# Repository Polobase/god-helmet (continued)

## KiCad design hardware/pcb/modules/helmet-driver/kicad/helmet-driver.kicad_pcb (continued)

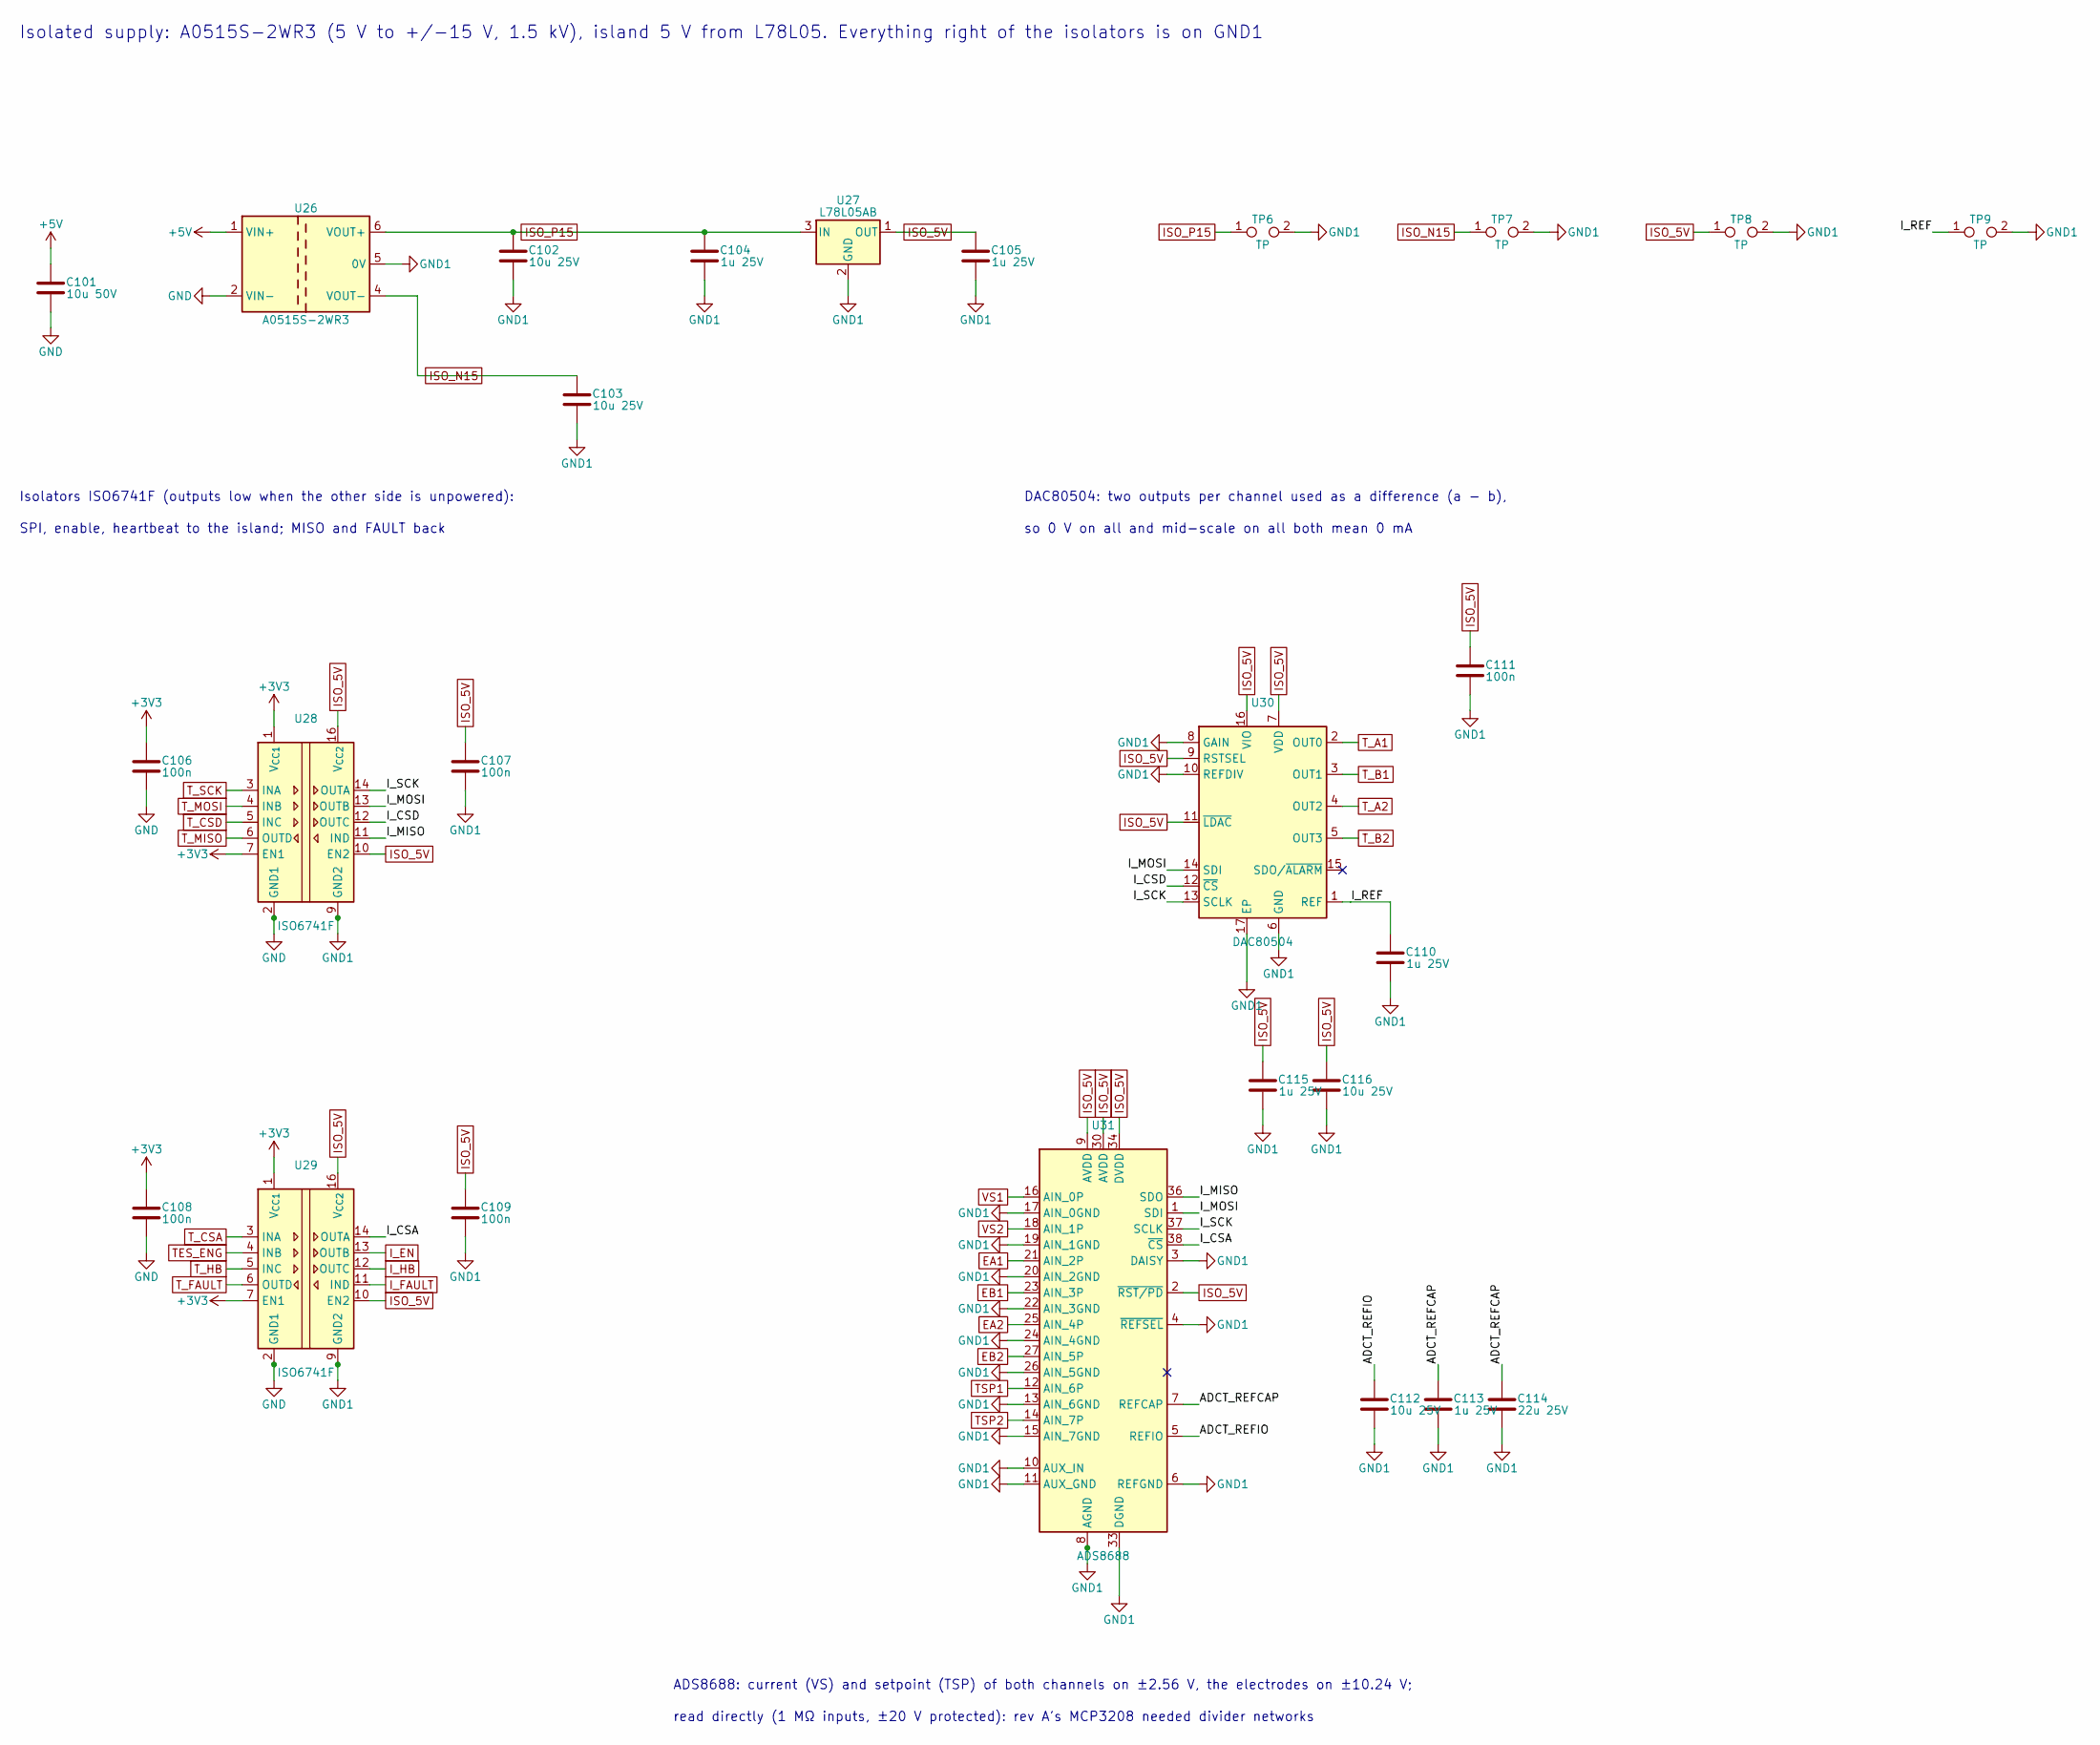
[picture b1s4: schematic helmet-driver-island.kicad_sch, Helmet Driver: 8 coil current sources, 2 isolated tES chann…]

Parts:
C101: 10u 50V; C_1206_3216Metric; MPN CL31A106KBHNNNE; LCSC C13585
C102, C103, C112, C116: 10u 25V; C_1210_3225Metric; MPN CL32B106KAJNNNE; LCSC C39232
C104, C105, C110, C113, C115: 1u 25V; C_0603_1608Metric; MPN CL10B105KA8NNNC; LCSC C29936
C106, C107, C108, C109, C111: 100n; C_0603_1608Metric; MPN CC0603KRX7R9BB104; LCSC C14663
C114: 22u 25V; C_1210_3225Metric; MPN CL32B226KAJNNNE; LCSC C309062
TP6, TP7, TP8, TP9: TP; TestPoint_2Pads_Pitch2.54mm_Drill0.8mm; PartKey testpoint-2pad
U26: A0515S-2WR3; Converter_DCDC_EVISUN_A0515S-2WR3_THT; MPN A0515S-2WR3; LCSC C7465204
U27: L78L05AB; SOT-89-3; MPN L78L05ABUTR; LCSC C42738
U28, U29: ISO6741F; SOIC-16W_7.5x10.3mm_P1.27mm; MPN ISO6741FDWR; LCSC C5216433
U30: DAC80504; Texas_RTE0016D_WQFN-16-1EP_3x3mm_P0.5mm_EP0.8x0.8mm_Thermal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; MPN DAC80504RTET; LCSC C2862796
U31: ADS8688; TSSOP-38_4.4x9.7mm_P0.5mm; MPN ADS8688IDBTR; LCSC C527390

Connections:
+3V3: C106.1, C108.1, U28.1 (V_{CC1}), U28.7 (EN1), U29.1 (V_{CC1}), U29.7 (EN1); also elsewhere on the board
+5V: C101.1, U26.1 (VIN+); also elsewhere on the board
/tES island: isolated power, isolators, DAC, ADC/ADCT_REFCAP: C113.1, C114.1, U31.7 (REFCAP)
/tES island: isolated power, isolators, DAC, ADC/ADCT_REFIO: C112.1, U31.5 (REFIO)
/tES island: isolated power, isolators, DAC, ADC/I_CSA: U29.14 (OUTA), U31.38 (~CS)
/tES island: isolated power, isolators, DAC, ADC/I_CSD: U28.12 (OUTC), U30.12 (~CS)
/tES island: isolated power, isolators, DAC, ADC/I_MISO: U28.11 (IND), U31.36 (SDO)
/tES island: isolated power, isolators, DAC, ADC/I_MOSI: U28.13 (OUTB), U30.14 (SDI), U31.1 (SDI)
/tES island: isolated power, isolators, DAC, ADC/I_REF: C110.1, TP9.1, U30.1 (REF)
/tES island: isolated power, isolators, DAC, ADC/I_SCK: U28.14 (OUTA), U30.13 (SCLK), U31.37 (SCLK)
EA1: U31.21 (AIN_2P); also elsewhere on the board
EA2: U31.25 (AIN_4P); also elsewhere on the board
EB1: U31.23 (AIN_3P); also elsewhere on the board
EB2: U31.27 (AIN_5P); also elsewhere on the board
GND: C101.2, C106.2, C108.2, U26.2 (VIN-), U28.2 (GND1), U28.8 (GND1), U29.2 (GND1), U29.8 (GND1); also elsewhere on the board
GND1: C102.2, C103.2, C104.2, C105.2, C107.2, C109.2, C110.2, C111.2, C112.2, C113.2, C114.2, C115.2, C116.2, TP6.2, TP7.2, TP8.2, TP9.2, U26.5 (0V), U27.2 (GND), U28.9 (GND2), U28.15 (GND2), U29.9 (GND2), U29.15 (GND2), U30.6 (GND), U30.8 (GAIN), U30.10 (REFDIV), U30.17 (EP), U31.3 (DAISY), U31.4 (~REFSEL), U31.6 (REFGND), U31.8 (AGND), U31.10 (AUX_IN), U31.11 (AUX_GND), U31.13 (AIN_6GND), U31.15 (AIN_7GND), U31.17 (AIN_0GND), U31.19 (AIN_1GND), U31.20 (AIN_2GND), U31.22 (AIN_3GND), U31.24 (AIN_4GND), U31.26 (AIN_5GND), U31.28 (AGND), U31.29 (AGND), U31.31 (AGND), U31.32 (AGND), U31.33 (DGND); also elsewhere on the board
ISO_5V: C105.1, C107.1, C109.1, C111.1, C115.1, C116.1, TP8.1, U27.1 (OUT), U28.10 (EN2), U28.16 (V_{CC2}), U29.10 (EN2), U29.16 (V_{CC2}), U30.7 (VDD), U30.9 (RSTSEL), U30.11 (~LDAC), U30.16 (VIO), U31.2 (~RST/PD), U31.9 (AVDD), U31.30 (AVDD), U31.34 (DVDD); also elsewhere on the board
ISO_N15: C103.1, TP7.1, U26.4 (VOUT-); also elsewhere on the board
ISO_P15: C102.1, C104.1, TP6.1, U26.6 (VOUT+), U27.3 (IN); also elsewhere on the board
I_EN: U29.13 (OUTB); also elsewhere on the board
I_FAULT: U29.11 (IND); also elsewhere on the board
I_HB: U29.12 (OUTC); also elsewhere on the board
TES_ENG: U29.4 (INB); also elsewhere on the board
TSP1: U31.12 (AIN_6P); also elsewhere on the board
TSP2: U31.14 (AIN_7P); also elsewhere on the board
T_A1: U30.2 (OUT0); also elsewhere on the board
T_A2: U30.4 (OUT2); also elsewhere on the board
T_B1: U30.3 (OUT1); also elsewhere on the board
T_B2: U30.5 (OUT3); also elsewhere on the board
T_CSA: U29.3 (INA); also elsewhere on the board
T_CSD: U28.5 (INC); also elsewhere on the board
T_FAULT: U29.6 (OUTD); also elsewhere on the board
T_HB: U29.5 (INC); also elsewhere on the board
T_MISO: U28.6 (OUTD); also elsewhere on the board
T_MOSI: U28.4 (INB); also elsewhere on the board
T_SCK: U28.3 (INA); also elsewhere on the board
VS1: U31.16 (AIN_0P); also elsewhere on the board
VS2: U31.18 (AIN_1P); also elsewhere on the board

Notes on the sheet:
read directly (1 MΩ inputs, ±20 V protected): rev A's MCP3208 needed divider networks
SPI, enable, heartbeat to the island; MISO and FAULT back
so 0 V on all and mid-scale on all both mean 0 mA
Isolated supply: A0515S-2WR3 (5 V to +/-15 V, 1.5 kV), island 5 V from L78L05. Everything right of the isolators is on GND1
Isolators ISO6741F (outputs low when the other side is unpowered):
DAC80504: two outputs per channel used as a difference (a - b),
ADS8688: current (VS) and setpoint (TSP) of both channels on ±2.56 V, the electrodes on ±10.24 V;

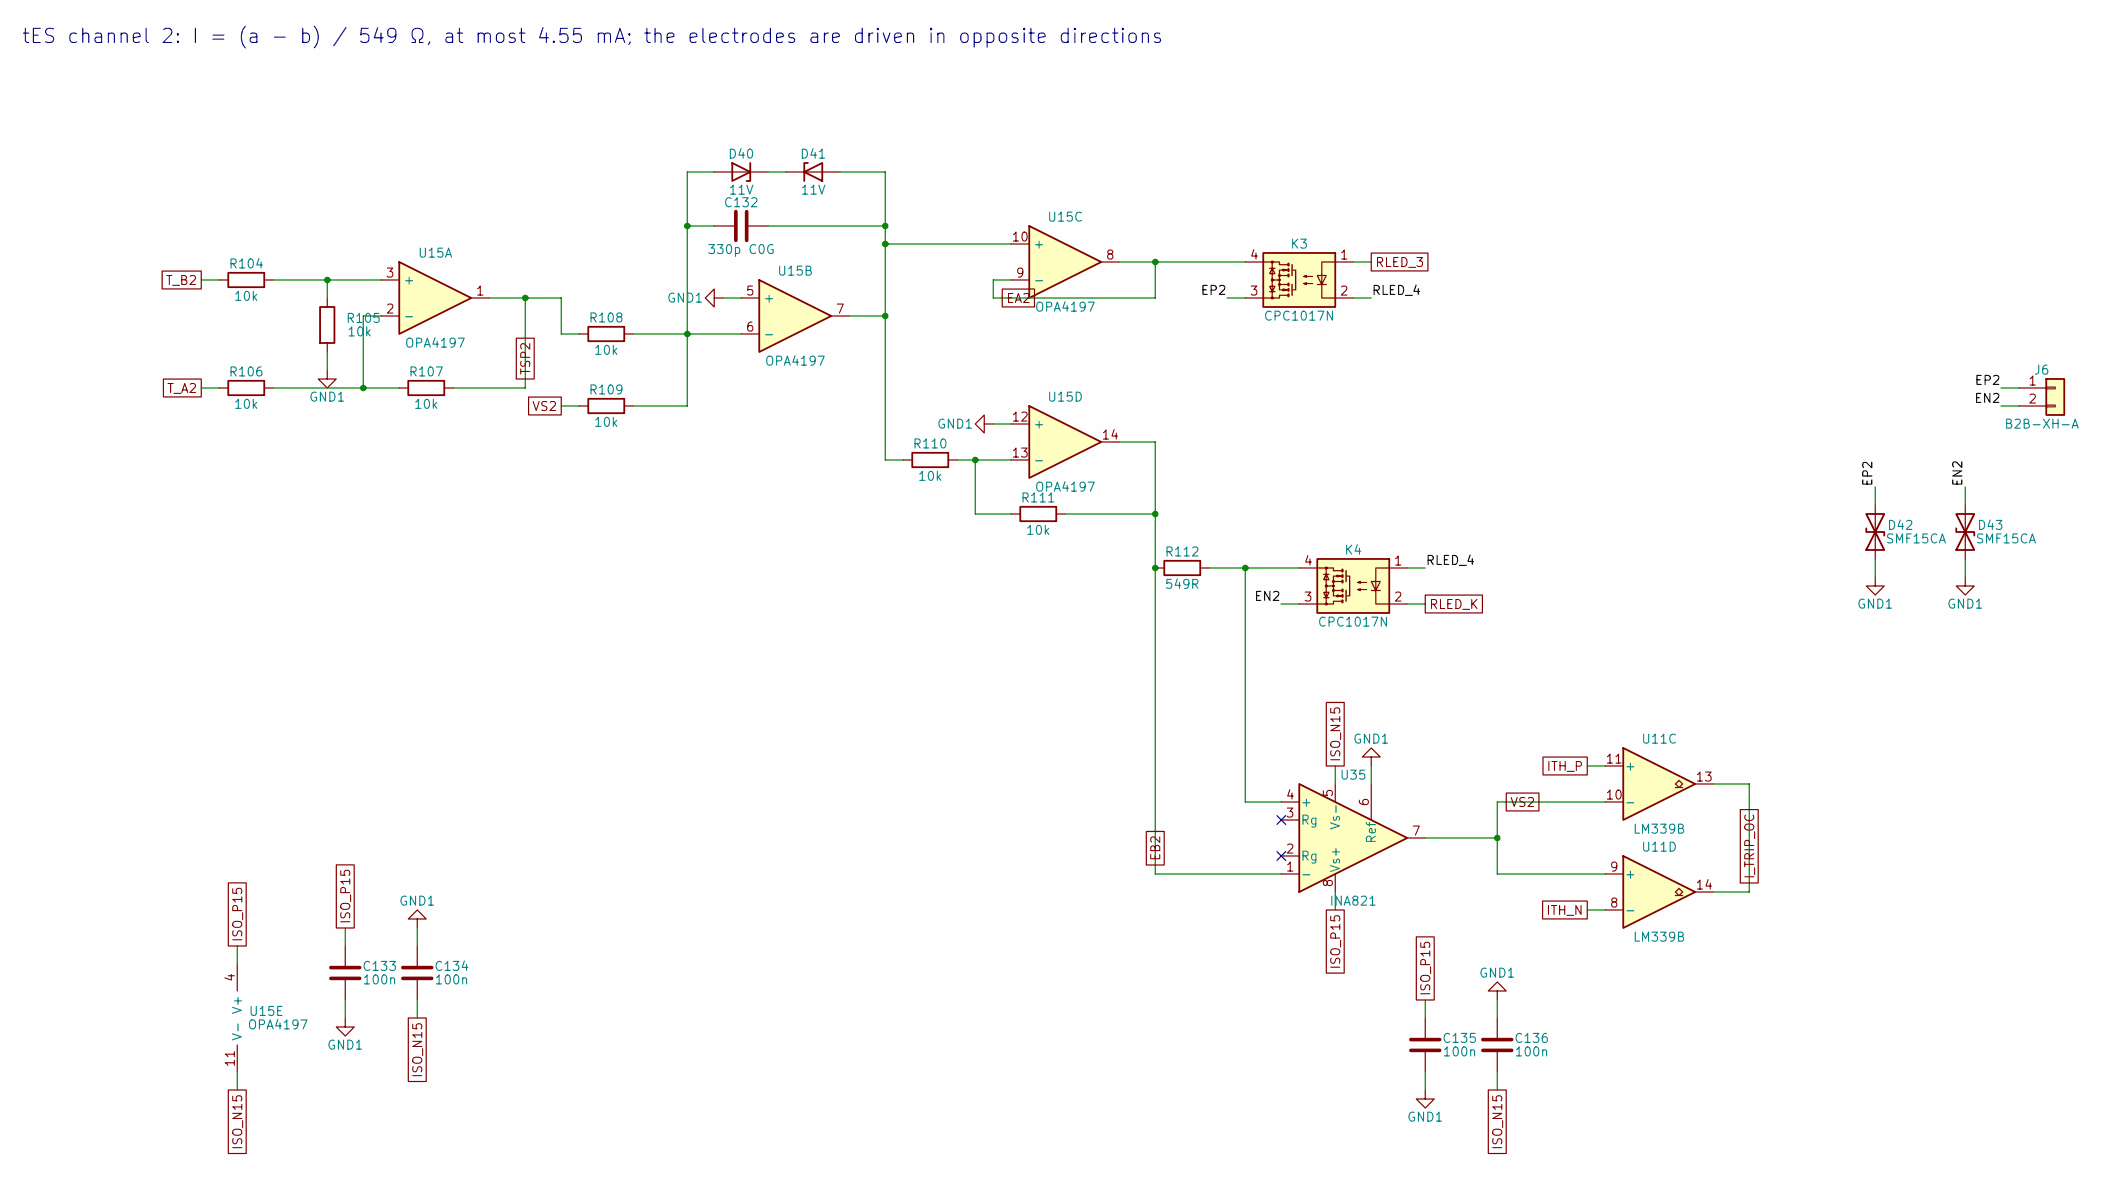
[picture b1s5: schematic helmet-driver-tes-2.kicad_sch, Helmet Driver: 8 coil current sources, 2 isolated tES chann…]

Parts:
C132: 330p C0G; C_0603_1608Metric; MPN 0603CG331J500NT; LCSC C190577
C133, C134, C135, C136: 100n; C_0603_1608Metric; MPN CC0603KRX7R9BB104; LCSC C14663
D40, D41: 11V; D_SOD-123; MPN BZT52C11-7-F; LCSC C92321
D42, D43: SMF15CA; D_SOD-123F; MPN SMF15CA; LCSC C1851361
J6: B2B-XH-A; JST_XH_B2B-XH-A_1x02_P2.50mm_Vertical; MPN B2B-XH-A(LF)(SN); LCSC C158012
K3, K4: CPC1017N; SOP-4_3.8x4.1mm_P2.54mm; MPN CPC1017NTR; LCSC C81521
R104, R110, R111: 10k; R_0603_1608Metric; MPN 0603WAF1002T5E; LCSC C25804
R105, R106, R107, R108, R109: 10k; R_0603_1608Metric; MPN RT0603BRD0710KL; LCSC C95204
R112: 549R; R_0603_1608Metric; MPN ARG03BTC5490; LCSC C5266143
U11: LM339B; SOIC-14_3.9x8.7mm_P1.27mm; MPN LM339BIDR; LCSC C22416291
U15: OPA4197; SOIC-14_3.9x8.7mm_P1.27mm; MPN OPA4197IDR; LCSC C2058532
U35: INA821; SOIC-8_3.9x4.9mm_P1.27mm; MPN INA821IDR; LCSC C2060822

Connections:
/tES channel 2/EN2: D43.2 (A2), J6.2, K4.3
/tES channel 2/EP2: D42.2 (A2), J6.1, K3.3
/tES channel 2/RLED_4: K3.2, K4.1
EA2: K3.4, U15.8, U15.9 (-); also elsewhere on the board
EB2: R111.2, R112.1, U15.14, U35.1 (-); also elsewhere on the board
GND1: C133.2, C134.1, C135.2, C136.1, D42.1 (A1), D43.1 (A1), R105.2, U15.5 (+), U15.12 (+), U35.6 (Ref); also elsewhere on the board
ISO_N15: C134.2, C136.2, U15.11 (V-), U35.5 (Vs-); also elsewhere on the board
ISO_P15: C133.1, C135.1, U15.4 (V+), U35.8 (Vs+); also elsewhere on the board
ITH_N: U11.8 (-); also elsewhere on the board
ITH_P: U11.11 (+); also elsewhere on the board
I_TRIP_OC: U11.13, U11.14; also elsewhere on the board
unnamed: C132.1, D40.2 (A), R108.2, R109.2, U15.6 (-)
unnamed: D40.1 (K), D41.1 (K)
unnamed: C132.2, D41.2 (A), R110.1, U15.7, U15.10 (+)
unnamed: R104.2, R105.1, U15.3 (+)
unnamed: R106.2, R107.1, U15.2 (-)
unnamed: R110.2, R111.1, U15.13 (-)
unnamed: K4.4, R112.2, U35.4 (+)
RLED_3: K3.1; also elsewhere on the board
RLED_K: K4.2; also elsewhere on the board
TSP2: R107.2, R108.1, U15.1; also elsewhere on the board
T_A2: R106.1; also elsewhere on the board
T_B2: R104.1; also elsewhere on the board
VS2: R109.1, U11.9 (+), U11.10 (-), U35.7; also elsewhere on the board

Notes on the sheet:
tES channel 2: I = (a - b) / 549 Ω, at most 4.55 mA; the electrodes are driven in opposite directions

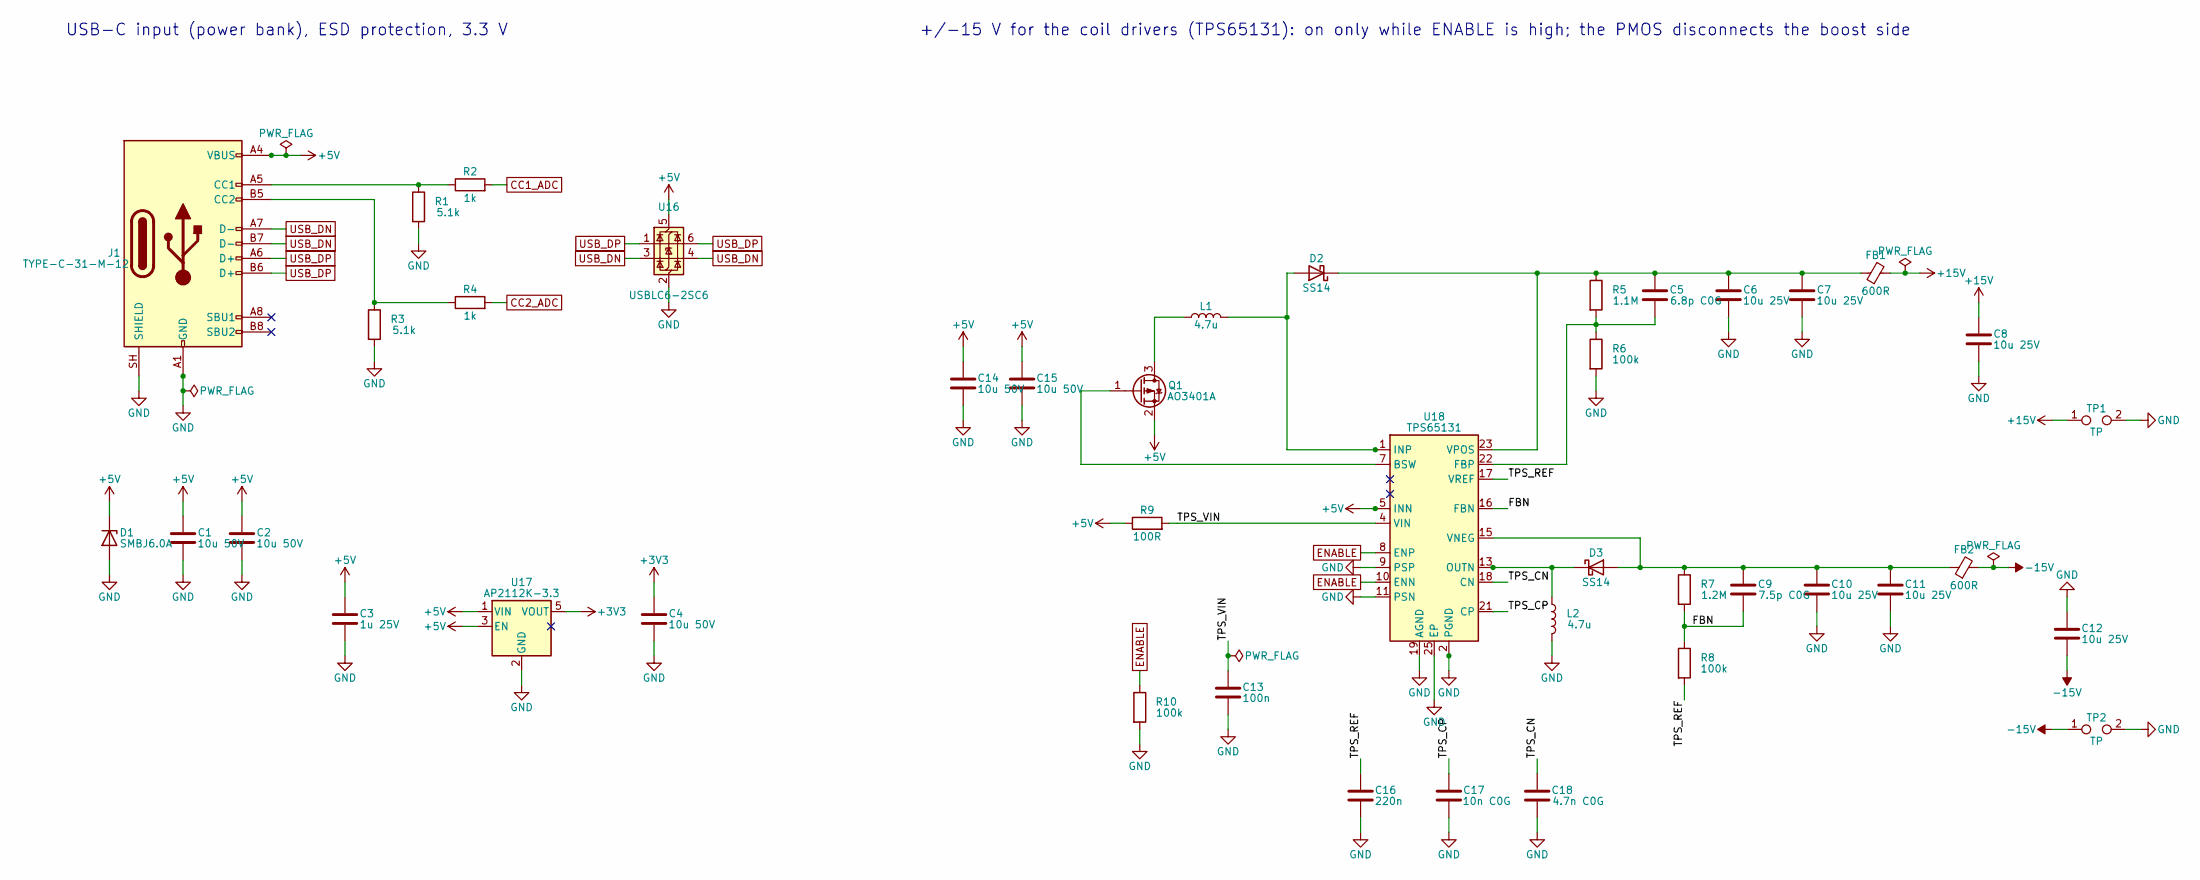
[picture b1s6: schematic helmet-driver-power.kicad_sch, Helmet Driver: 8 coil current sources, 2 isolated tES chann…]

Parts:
C1, C2, C4, C14, C15: 10u 50V; C_1206_3216Metric; MPN CL31A106KBHNNNE; LCSC C13585
C3: 1u 25V; C_0603_1608Metric; MPN CL10B105KA8NNNC; LCSC C29936
C5: 6.8p C0G; C_0603_1608Metric; MPN 0603CG6R8C500NT; LCSC C1679
C6, C7, C8, C10, C11, C12: 10u 25V; C_1210_3225Metric; MPN CL32B106KAJNNNE; LCSC C39232
C9: 7.5p C0G; C_0603_1608Metric; MPN 0603CG7R5C500NT; LCSC C53424
C13: 100n; C_0603_1608Metric; MPN CC0603KRX7R9BB104; LCSC C14663
C16: 220n; C_0603_1608Metric; MPN CL10B224KB8NNNC; LCSC C64705
C17: 10n C0G; C_0603_1608Metric; MPN GRM1885C1H103JA01D; LCSC C85973
C18: 4.7n C0G; C_0603_1608Metric; MPN GRM1885C1H472JA01D; LCSC C85980
D1: SMBJ6.0A; D_SMB; MPN SMBJ6.0A; LCSC C19077560
D2, D3: SS14; D_SMA; MPN SS14; LCSC C2480
FB1, FB2: 600R; L_0805_2012Metric; MPN GZ2012D601TF; LCSC C1017
J1: TYPE-C-31-M-12; USB_C_Receptacle_HRO_TYPE-C-31-M-12; MPN TYPE-C-31-M-12; LCSC C165948
L1, L2: 4.7u; L_Sunlord_SWPA6045S; MPN SWPA6045S4R7MT; LCSC C78804
Q1: AO3401A; SOT-23; MPN AO3401A; LCSC C15127
R1, R3: 5.1k; R_0603_1608Metric; MPN 0603WAF5101T5E; LCSC C23186
R2, R4: 1k; R_0603_1608Metric; MPN 0603WAF1001T5E; LCSC C21190
R5: 1.1M; R_0603_1608Metric; MPN 0603WAF1104T5E; LCSC C13314
R6, R8, R10: 100k; R_0603_1608Metric; MPN 0603WAF1003T5E; LCSC C25803
R7: 1.2M; R_0603_1608Metric; MPN 0603WAF1204T5E; LCSC C13315
R9: 100R; R_0603_1608Metric; MPN 0603WAF1000T5E; LCSC C22775
TP1, TP2: TP; TestPoint_2Pads_Pitch2.54mm_Drill0.8mm; PartKey testpoint-2pad
U16: USBLC6-2SC6; SOT-23-6; MPN USBLC6-2SC6; LCSC C7519
U17: AP2112K-3.3; SOT-23-5; MPN AP2112K-3.3TRG1; LCSC C51118
U18: TPS65131; VQFN-24-1EP_4x4mm_P0.5mm_EP2.45x2.45mm_ThermalVias; MPN TPS65131RGER; LCSC C87663

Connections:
+3V3: C4.1, U17.5 (VOUT); also elsewhere on the board
+5V: C1.1, C2.1, C3.1, C14.1, C15.1, D1.1 (K), J1.A4 (VBUS), J1.A9 (VBUS), J1.B4 (VBUS), J1.B9 (VBUS), Q1.2 (S), R9.1, U16.5 (VBUS), U17.1 (VIN), U17.3 (EN), U18.5 (INN), U18.6 (INN); also elsewhere on the board
+15V: C8.1, FB1.2, TP1.1; also elsewhere on the board
-15V: C12.2, FB2.2, TP2.1; also elsewhere on the board
/Power: USB-C input, 3.3 V, ±15 V for the coil drivers/FBN: C9.2, R7.2, R8.1, U18.16 (FBN)
/Power: USB-C input, 3.3 V, ±15 V for the coil drivers/TPS_CN: C18.1, U18.18 (CN)
/Power: USB-C input, 3.3 V, ±15 V for the coil drivers/TPS_CP: C17.1, U18.21 (CP)
/Power: USB-C input, 3.3 V, ±15 V for the coil drivers/TPS_REF: C16.1, R8.2, U18.17 (VREF)
/Power: USB-C input, 3.3 V, ±15 V for the coil drivers/TPS_VIN: C13.1, R9.2, U18.4 (VIN)
CC1_ADC: R2.2; also elsewhere on the board
CC2_ADC: R4.2; also elsewhere on the board
ENABLE: R10.1, U18.8 (ENP), U18.10 (ENN); also elsewhere on the board
GND: C1.2, C2.2, C3.2, C4.2, C6.2, C7.2, C8.2, C10.2, C11.2, C12.1, C13.2, C14.2, C15.2, C16.2, C17.2, C18.2, D1.2 (A), J1.A1 (GND), J1.A12 (GND), J1.B1 (GND), J1.B12 (GND), J1.SH (SHIELD), L2.2, R1.2, R3.2, R6.2, R10.2, TP1.2, TP2.2, U16.2 (GND), U17.2 (GND), U18.2 (PGND), U18.3 (PGND), U18.9 (PSP), U18.11 (PSN), U18.19 (AGND), U18.25 (EP); also elsewhere on the board
unnamed: D2.2 (A), L1.2, U18.1 (INP), U18.24 (INP)
unnamed: C5.1, C6.1, C7.1, D2.1 (K), FB1.1, R5.1, U18.23 (VPOS)
unnamed: C9.1, C10.1, C11.1, D3.2 (A), FB2.1, R7.1, U18.15 (VNEG)
unnamed: D3.1 (K), L2.1, U18.13 (OUTN), U18.14 (OUTN)
unnamed: J1.A5 (CC1), R1.1, R2.1
unnamed: J1.B5 (CC2), R3.1, R4.1
unnamed: L1.1, Q1.3 (D)
unnamed: Q1.1 (G), U18.7 (BSW)
unnamed: C5.2, R5.2, R6.1, U18.22 (FBP)
USB_DN: J1.A7 (D-), J1.B7 (D-), U16.3 (I/O2), U16.4 (I/O2); also elsewhere on the board
USB_DP: J1.A6 (D+), J1.B6 (D+), U16.1 (I/O1), U16.6 (I/O1); also elsewhere on the board

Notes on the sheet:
+/-15 V for the coil drivers (TPS65131): on only while ENABLE is high; the PMOS disconnects the boost side
USB-C input (power bank), ESD protection, 3.3 V

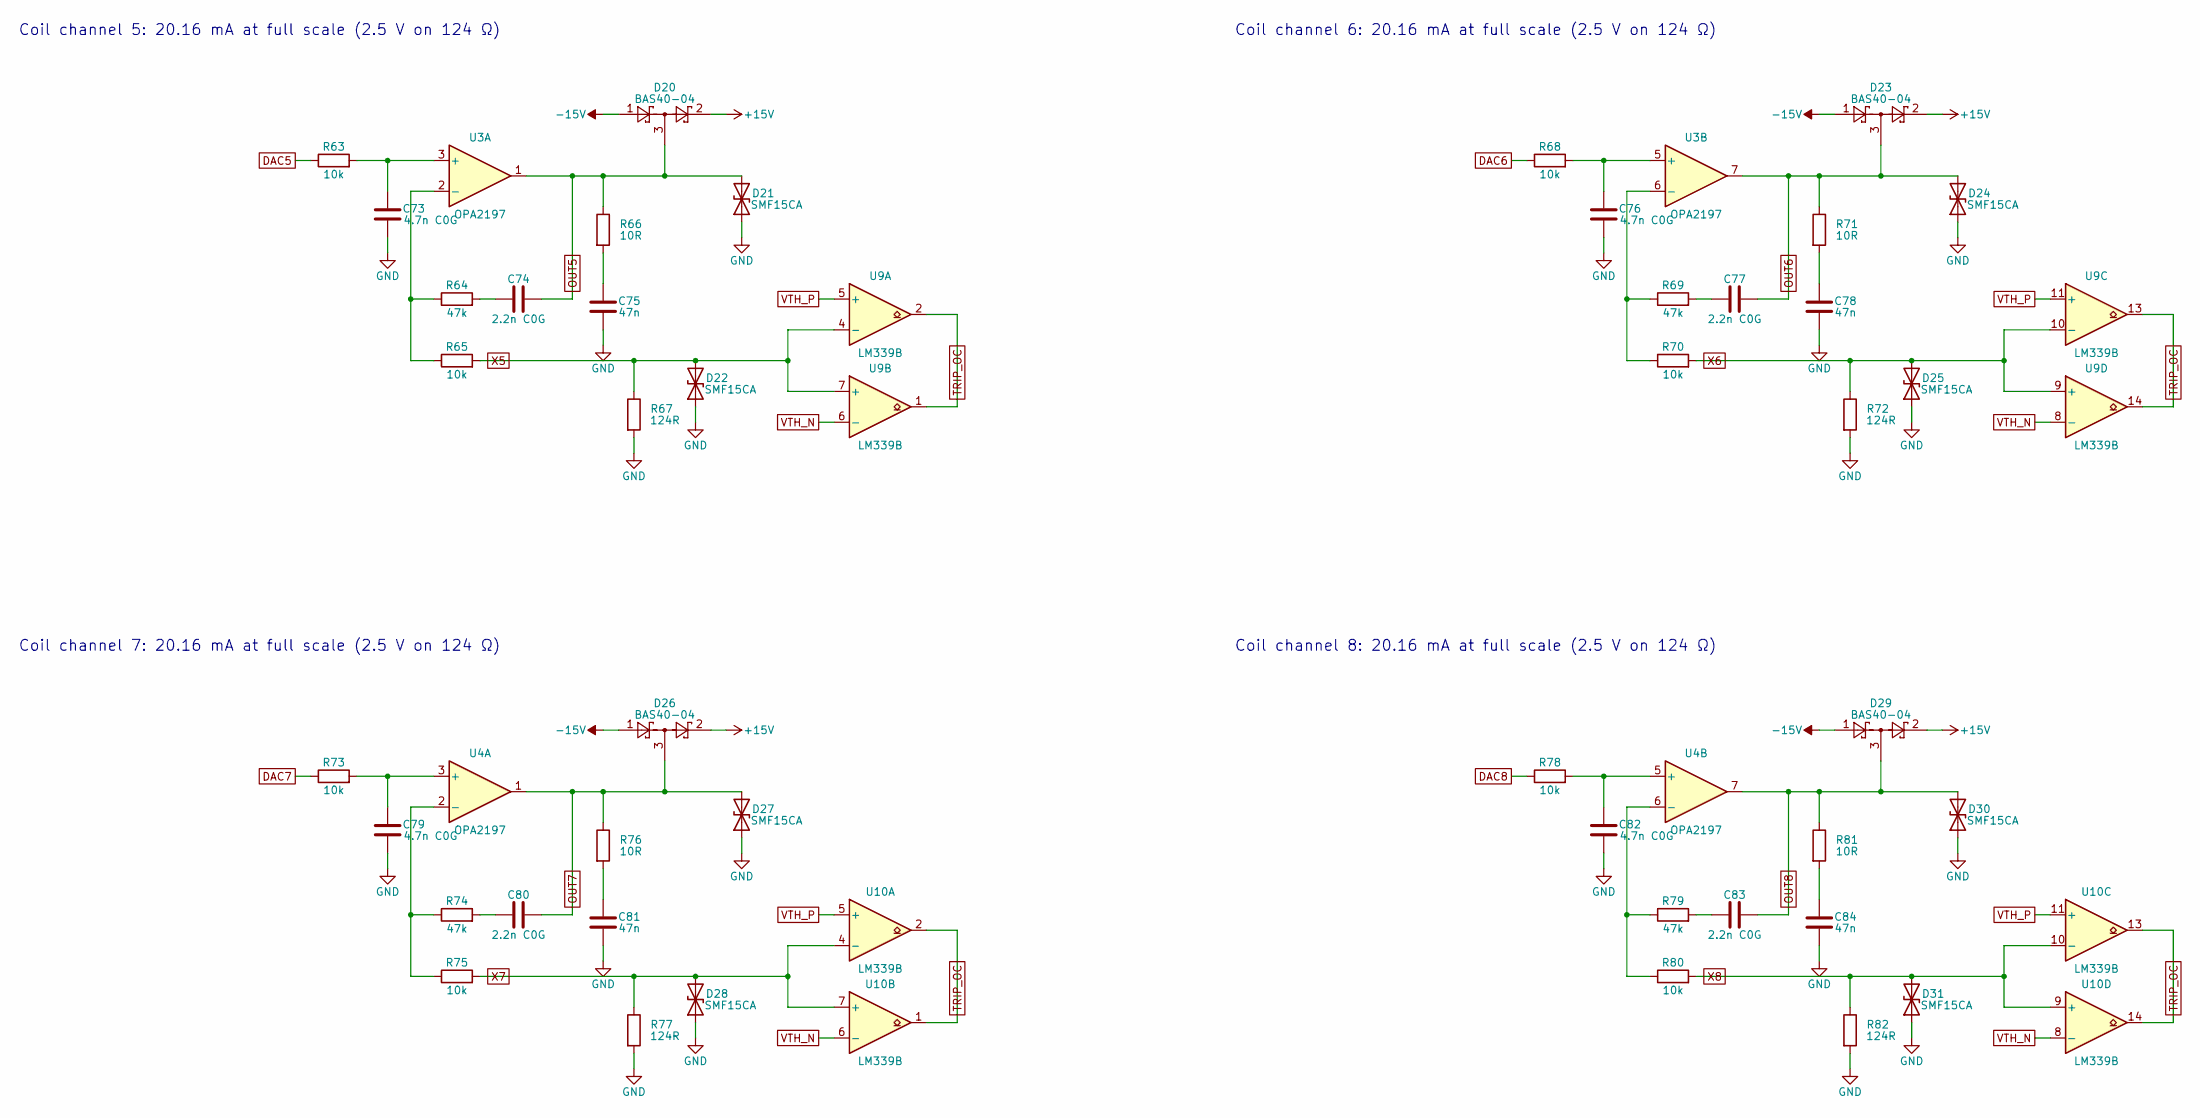
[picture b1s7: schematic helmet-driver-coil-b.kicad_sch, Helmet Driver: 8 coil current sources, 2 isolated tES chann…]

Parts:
C73, C76, C79, C82: 4.7n C0G; C_0603_1608Metric; MPN GRM1885C1H472JA01D; LCSC C85980
C74, C77, C80, C83: 2.2n C0G; C_0603_1608Metric; MPN 0603CG222J500NT; LCSC C2991172
C75, C78, C81, C84: 47n; C_0603_1608Metric; MPN CL10B473KB8NNNC; LCSC C1622
D20, D23, D26, D29: BAS40-04; SOT-23; MPN BAS40-04LT1G; LCSC C78265
D21, D22, D24, D25, D27, D28, D30, D31: SMF15CA; D_SOD-123F; MPN SMF15CA; LCSC C1851361
R63, R65, R68, R70, R73, R75, R78, R80: 10k; R_0603_1608Metric; MPN 0603WAF1002T5E; LCSC C25804
R64, R69, R74, R79: 47k; R_0603_1608Metric; MPN 0603WAF4702T5E; LCSC C25819
R66, R71, R76, R81: 10R; R_0603_1608Metric; MPN 0603WAF100JT5E; LCSC C22859
R67, R72, R77, R82: 124R; R_0603_1608Metric; MPN RN73H1JTTD1240B25; LCSC C346154
U3, U4: OPA2197; SOIC-8_3.9x4.9mm_P1.27mm; MPN OPA2197IDR; LCSC C139363
U9, U10: LM339B; SOIC-14_3.9x8.7mm_P1.27mm; MPN LM339BIDR; LCSC C22416291

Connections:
+15V: D20.2, D23.2, D26.2, D29.2; also elsewhere on the board
-15V: D20.1, D23.1, D26.1, D29.1; also elsewhere on the board
DAC5: R63.1; also elsewhere on the board
DAC6: R68.1; also elsewhere on the board
DAC7: R73.1; also elsewhere on the board
DAC8: R78.1; also elsewhere on the board
GND: C73.2, C75.2, C76.2, C78.2, C79.2, C81.2, C82.2, C84.2, D21.1 (A1), D22.1 (A1), D24.1 (A1), D25.1 (A1), D27.1 (A1), D28.1 (A1), D30.1 (A1), D31.1 (A1), R67.2, R72.2, R77.2, R82.2; also elsewhere on the board
unnamed: C74.1, R64.2
unnamed: C75.1, R66.2
unnamed: C77.1, R69.2
unnamed: C78.1, R71.2
unnamed: C80.1, R74.2
unnamed: C81.1, R76.2
unnamed: C83.1, R79.2
unnamed: C84.1, R81.2
unnamed: C73.1, R63.2, U3.3 (+)
unnamed: R64.1, R65.1, U3.2 (-)
unnamed: C76.1, R68.2, U3.5 (+)
unnamed: R69.1, R70.1, U3.6 (-)
unnamed: C79.1, R73.2, U4.3 (+)
unnamed: R74.1, R75.1, U4.2 (-)
unnamed: C82.1, R78.2, U4.5 (+)
unnamed: R79.1, R80.1, U4.6 (-)
OUT5: C74.2, D20.3, D21.2 (A2), R66.1, U3.1; also elsewhere on the board
OUT6: C77.2, D23.3, D24.2 (A2), R71.1, U3.7; also elsewhere on the board
OUT7: C80.2, D26.3, D27.2 (A2), R76.1, U4.1; also elsewhere on the board
OUT8: C83.2, D29.3, D30.2 (A2), R81.1, U4.7; also elsewhere on the board
TRIP_OC: U9.1, U9.2, U9.13, U9.14, U10.1, U10.2, U10.13, U10.14; also elsewhere on the board
VTH_N: U9.6 (-), U9.8 (-), U10.6 (-), U10.8 (-); also elsewhere on the board
VTH_P: U9.5 (+), U9.11 (+), U10.5 (+), U10.11 (+); also elsewhere on the board
X5: D22.2 (A2), R65.2, R67.1, U9.4 (-), U9.7 (+); also elsewhere on the board
X6: D25.2 (A2), R70.2, R72.1, U9.9 (+), U9.10 (-); also elsewhere on the board
X7: D28.2 (A2), R75.2, R77.1, U10.4 (-), U10.7 (+); also elsewhere on the board
X8: D31.2 (A2), R80.2, R82.1, U10.9 (+), U10.10 (-); also elsewhere on the board

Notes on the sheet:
Coil channel 7: 20.16 mA at full scale (2.5 V on 124 Ω)
Coil channel 8: 20.16 mA at full scale (2.5 V on 124 Ω)
Coil channel 6: 20.16 mA at full scale (2.5 V on 124 Ω)
Coil channel 5: 20.16 mA at full scale (2.5 V on 124 Ω)

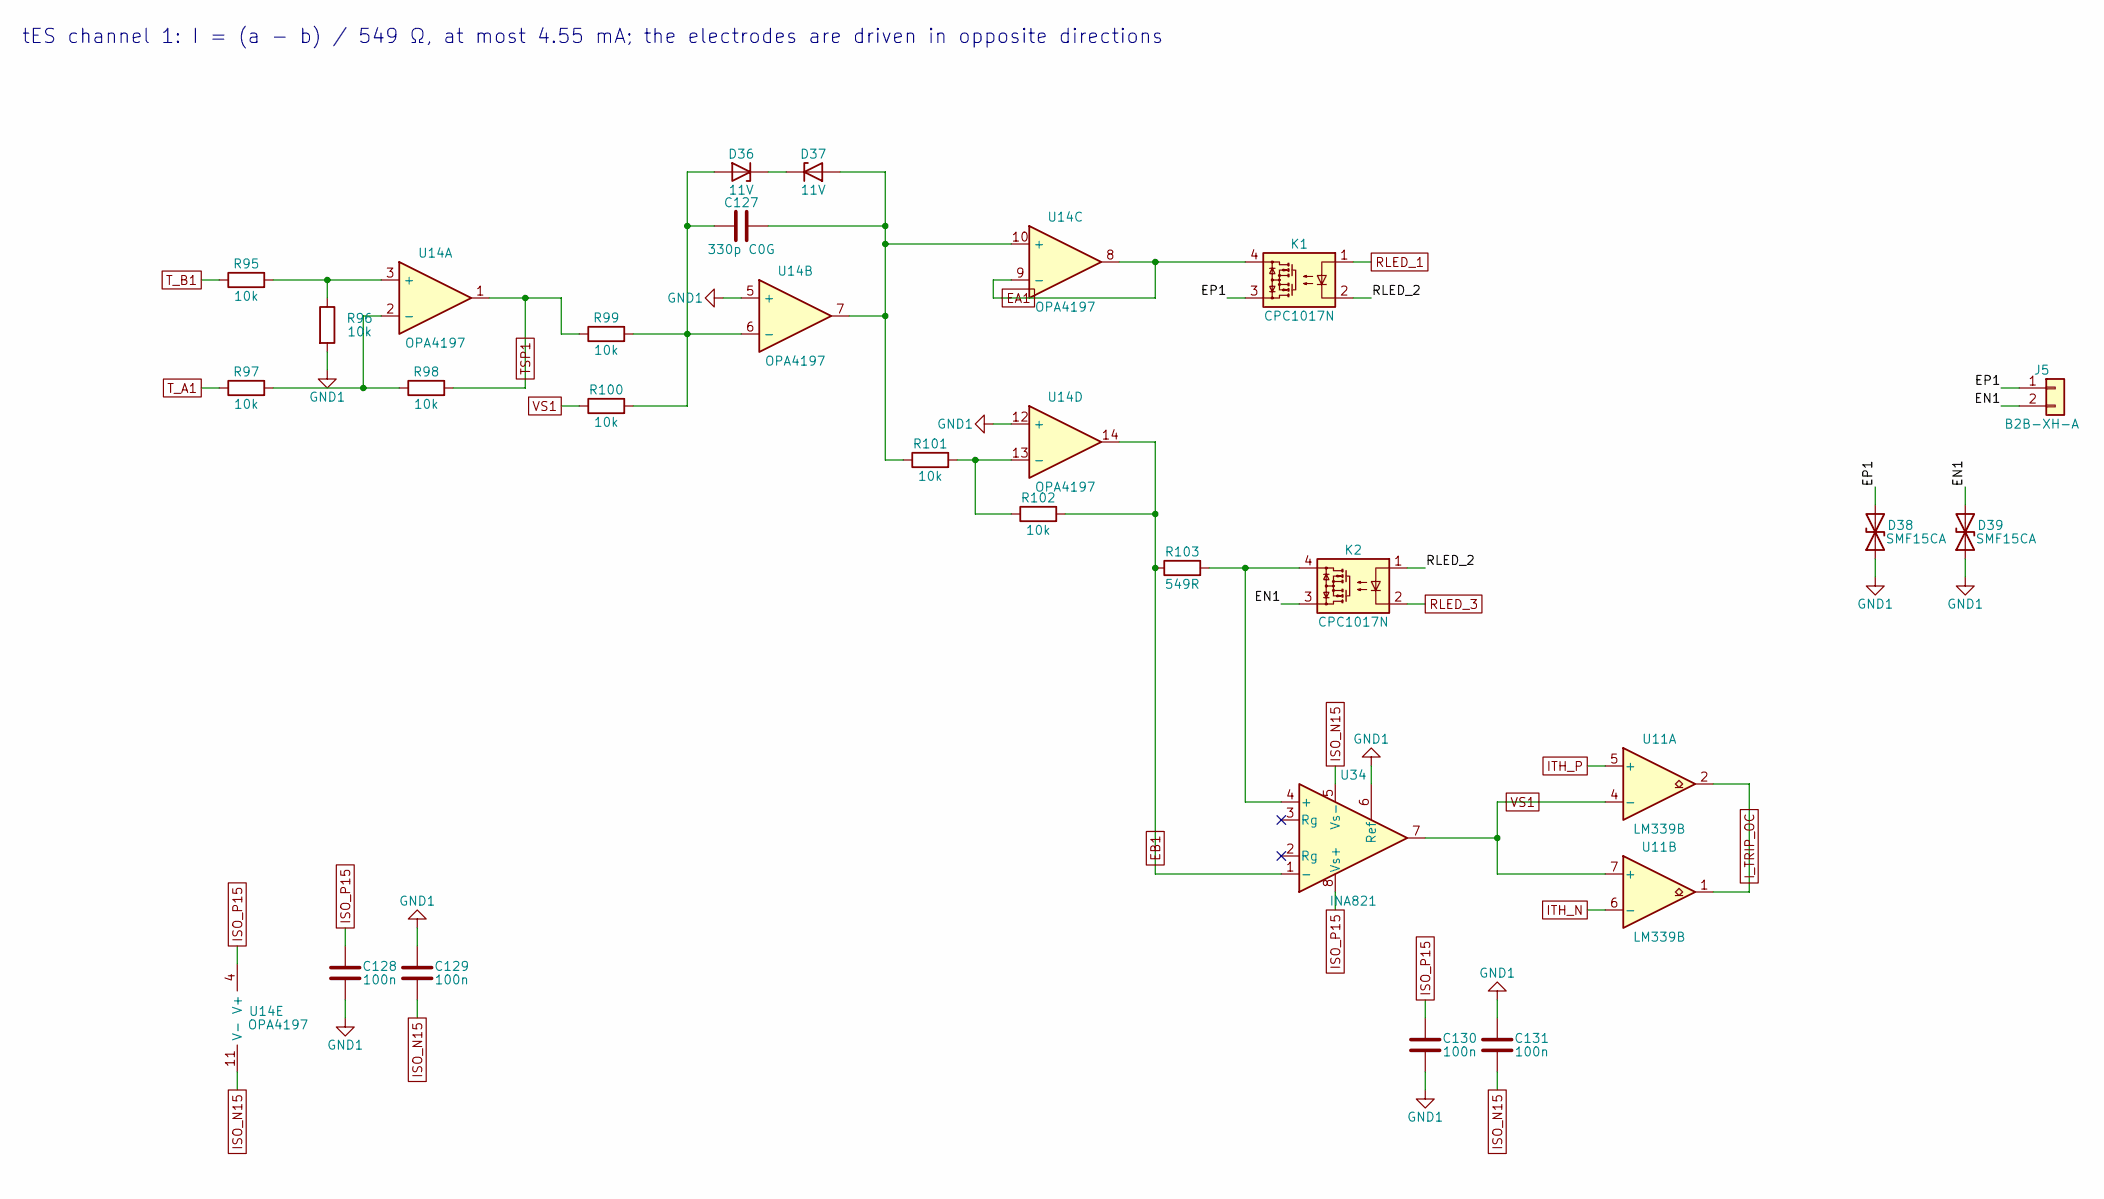
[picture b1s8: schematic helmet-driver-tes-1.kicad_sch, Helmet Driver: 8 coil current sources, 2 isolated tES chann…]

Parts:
C127: 330p C0G; C_0603_1608Metric; MPN 0603CG331J500NT; LCSC C190577
C128, C129, C130, C131: 100n; C_0603_1608Metric; MPN CC0603KRX7R9BB104; LCSC C14663
D36, D37: 11V; D_SOD-123; MPN BZT52C11-7-F; LCSC C92321
D38, D39: SMF15CA; D_SOD-123F; MPN SMF15CA; LCSC C1851361
J5: B2B-XH-A; JST_XH_B2B-XH-A_1x02_P2.50mm_Vertical; MPN B2B-XH-A(LF)(SN); LCSC C158012
K1, K2: CPC1017N; SOP-4_3.8x4.1mm_P2.54mm; MPN CPC1017NTR; LCSC C81521
R95, R101, R102: 10k; R_0603_1608Metric; MPN 0603WAF1002T5E; LCSC C25804
R96, R97, R98, R99, R100: 10k; R_0603_1608Metric; MPN RT0603BRD0710KL; LCSC C95204
R103: 549R; R_0603_1608Metric; MPN ARG03BTC5490; LCSC C5266143
U11: LM339B; SOIC-14_3.9x8.7mm_P1.27mm; MPN LM339BIDR; LCSC C22416291
U14: OPA4197; SOIC-14_3.9x8.7mm_P1.27mm; MPN OPA4197IDR; LCSC C2058532
U34: INA821; SOIC-8_3.9x4.9mm_P1.27mm; MPN INA821IDR; LCSC C2060822

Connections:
/tES channel 1/EN1: D39.2 (A2), J5.2, K2.3
/tES channel 1/EP1: D38.2 (A2), J5.1, K1.3
/tES channel 1/RLED_2: K1.2, K2.1
EA1: K1.4, U14.8, U14.9 (-); also elsewhere on the board
EB1: R102.2, R103.1, U14.14, U34.1 (-); also elsewhere on the board
GND1: C128.2, C129.1, C130.2, C131.1, D38.1 (A1), D39.1 (A1), R96.2, U14.5 (+), U14.12 (+), U34.6 (Ref); also elsewhere on the board
ISO_N15: C129.2, C131.2, U14.11 (V-), U34.5 (Vs-); also elsewhere on the board
ISO_P15: C128.1, C130.1, U14.4 (V+), U34.8 (Vs+); also elsewhere on the board
ITH_N: U11.6 (-); also elsewhere on the board
ITH_P: U11.5 (+); also elsewhere on the board
I_TRIP_OC: U11.1, U11.2; also elsewhere on the board
unnamed: C127.1, D36.2 (A), R99.2, R100.2, U14.6 (-)
unnamed: D36.1 (K), D37.1 (K)
unnamed: C127.2, D37.2 (A), R101.1, U14.7, U14.10 (+)
unnamed: R95.2, R96.1, U14.3 (+)
unnamed: R97.2, R98.1, U14.2 (-)
unnamed: R101.2, R102.1, U14.13 (-)
unnamed: K2.4, R103.2, U34.4 (+)
RLED_1: K1.1; also elsewhere on the board
RLED_3: K2.2; also elsewhere on the board
TSP1: R98.2, R99.1, U14.1; also elsewhere on the board
T_A1: R97.1; also elsewhere on the board
T_B1: R95.1; also elsewhere on the board
VS1: R100.1, U11.4 (-), U11.7 (+), U34.7; also elsewhere on the board

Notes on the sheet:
tES channel 1: I = (a - b) / 549 Ω, at most 4.55 mA; the electrodes are driven in opposite directions
